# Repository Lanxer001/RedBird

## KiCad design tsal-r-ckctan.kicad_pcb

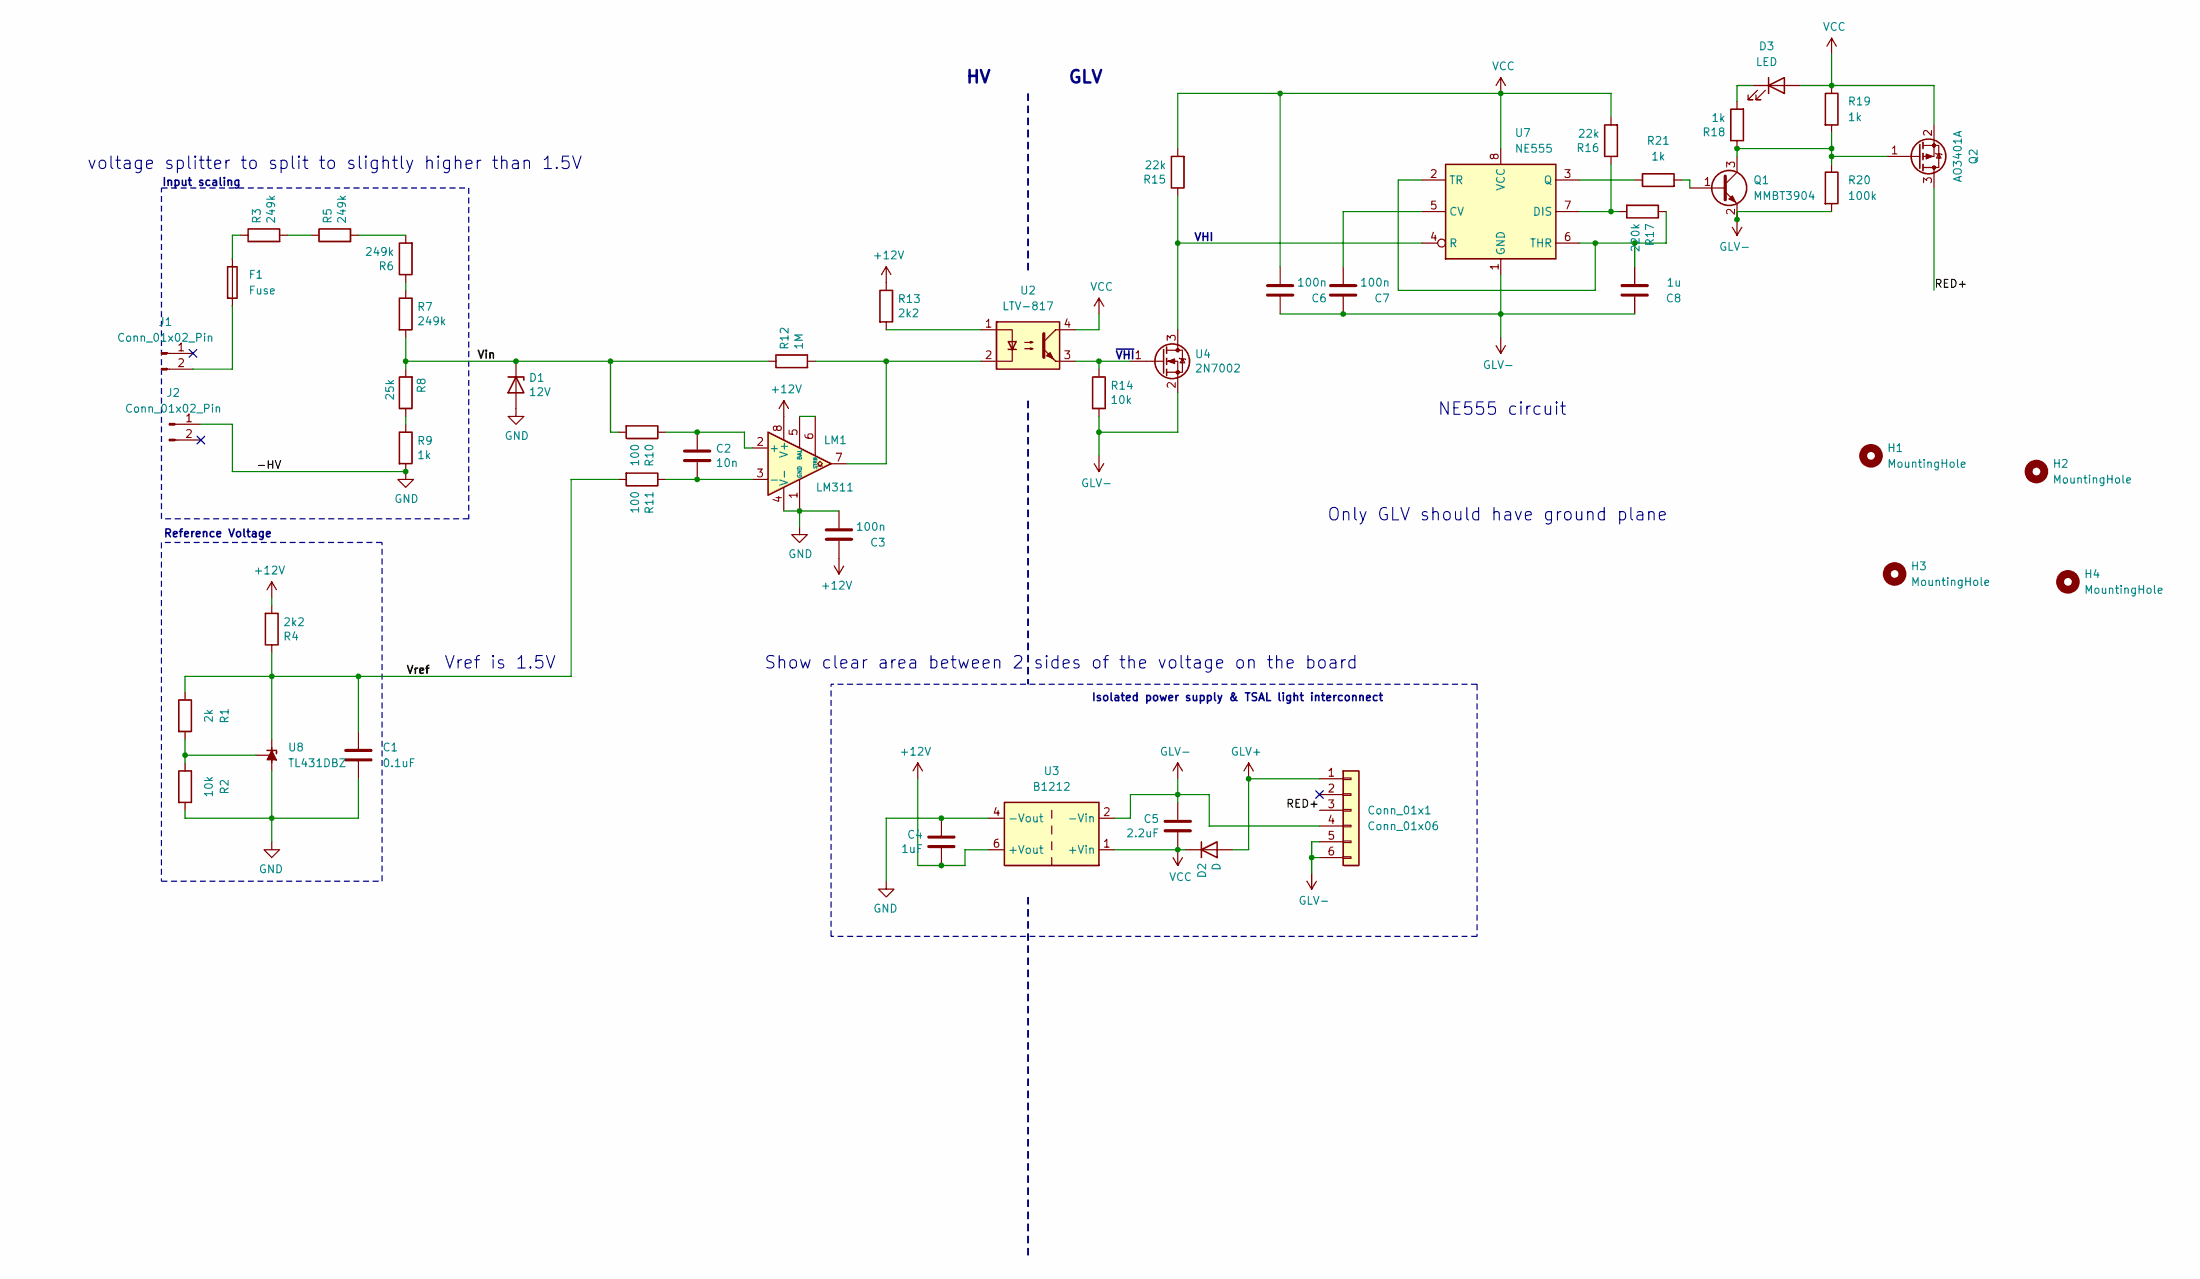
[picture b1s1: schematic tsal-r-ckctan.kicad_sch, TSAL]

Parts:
C1: 0.1uF; C_0805_2012Metric
C2: 10n; C_0805_2012Metric
C3, C6, C7: 100n; C_0805_2012Metric
C4: 1uF; C_0805_2012Metric
C5: 2.2uF; C_0805_2012Metric
C8: 1u; C_0805_2012Metric
Conn_01x1: Conn_01x06; JST_VH_B6P-VH_1x06_P3.96mm_Vertical
D1: 12V; D_DO-35_SOD27_P7.62mm_Horizontal
D2: D; D_SMA
D3: LED; LED_0805_2012Metric
F1: Fuse; Fuse_0805_2012Metric
H1, H2, H3, H4: MountingHole; MountingHole_2.2mm_M2
J1, J2: Conn_01x02_Pin; AMASS_XT60-M_1x02_P7.20mm_Vertical
LM1: LM311; LM311P
Q1: MMBT3904; SOT-23
Q2: AO3401A; SOT-23
R1: 2k; R_0805_2012Metric
R2, R14: 10k; R_0805_2012Metric
R3, R5, R6, R7: 249k; R_0805_2012Metric
R4, R13: 2k2; R_0805_2012Metric
R8: 25k; R_0805_2012Metric
R9, R18, R19, R21: 1k; R_0805_2012Metric
R10, R11: 100; R_0805_2012Metric
R12: 1M; R_0805_2012Metric
R15, R16: 22k; R_0805_2012Metric
R17: 220k; R_0805_2012Metric
R20: 100k; R_0805_2012Metric
U2: LTV-817; LTV-814
U3: B1212; Converter_DCDC_TRACO_TBA2-xxxx_Single_THT
U4: 2N7002; SOT-23TO-236_318-08_ONS
U7: NE555; SOIC-8_3.9x4.9mm_P1.27mm
U8: TL431DBZ; SOT-23

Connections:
+12V: C3.1, C4.2, LM1.8 (V+), R4.2, R13.1, U3.6 (+Vout)
/RED+: Conn_01x1.3, Q2.3 (D); also elsewhere on the board
/Vin: D1.1 (K), R7.2, R8.2, R10.2, R12.1
/Vref: C1.1, R1.1, R4.1, R11.2, U8.1 (K)
GLV+: Conn_01x1.1, D2.2 (A)
GLV-: C5.1, C6.1, C7.1, C8.1, Conn_01x1.4, Conn_01x1.5, Conn_01x1.6, Q1.2 (E), R14.2, R20.2, U3.2 (-Vin), U4.2 (S), U7.1 (GND); also elsewhere on the board
GND: C1.2, C3.2, C4.1, D1.2 (A), J2.1, LM1.1 (GND), LM1.4 (V-), R2.2, R9.2, U3.4 (-Vout), U8.3 (A)
unnamed: D3.1 (K), R18.2
unnamed: F1.1, R3.1
unnamed: F1.2, J1.2
unnamed: C2.1, LM1.2 (+), R10.1
unnamed: C2.2, LM1.3 (-), R11.1
unnamed: LM1.5 (BAL), LM1.6 (STRB)
unnamed: LM1.7, R12.2, U2.2
unnamed: Q1.1 (B), R21.2
unnamed: Q1.3 (C), Q2.1 (G), R18.1, R19.2, R20.1
unnamed: R3.2, R5.1
unnamed: R5.2, R6.2
unnamed: R6.1, R7.1
unnamed: R8.1, R9.1
unnamed: R13.2, U2.1
unnamed: R15.1, U4.3 (D), U7.4 (R)
unnamed: R14.1, U2.3, U4.1 (G)
unnamed: C7.2, U7.5 (CV)
unnamed: R16.1, R17.2, U7.7 (DIS)
unnamed: R21.1, U7.3 (Q)
unnamed: C8.2, R17.1, U7.2 (TR), U7.6 (THR)
unnamed: R1.2, R2.1, U8.2 (REF)
VCC: C5.2, C6.2, D2.1 (K), D3.2 (A), Q2.2 (S), R15.2, R16.2, R19.1, U2.4, U3.1 (+Vin), U7.8 (VCC)

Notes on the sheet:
voltage splitter to split to slightly higher than 1.5V
Show clear area between 2 sides of the voltage on the board
Isolated power supply & TSAL light interconnect
Reference Voltage
~{VHI}
Input scaling
Only GLV should have ground plane
GLV
VHI
Vref is 1.5V
NE555 circuit

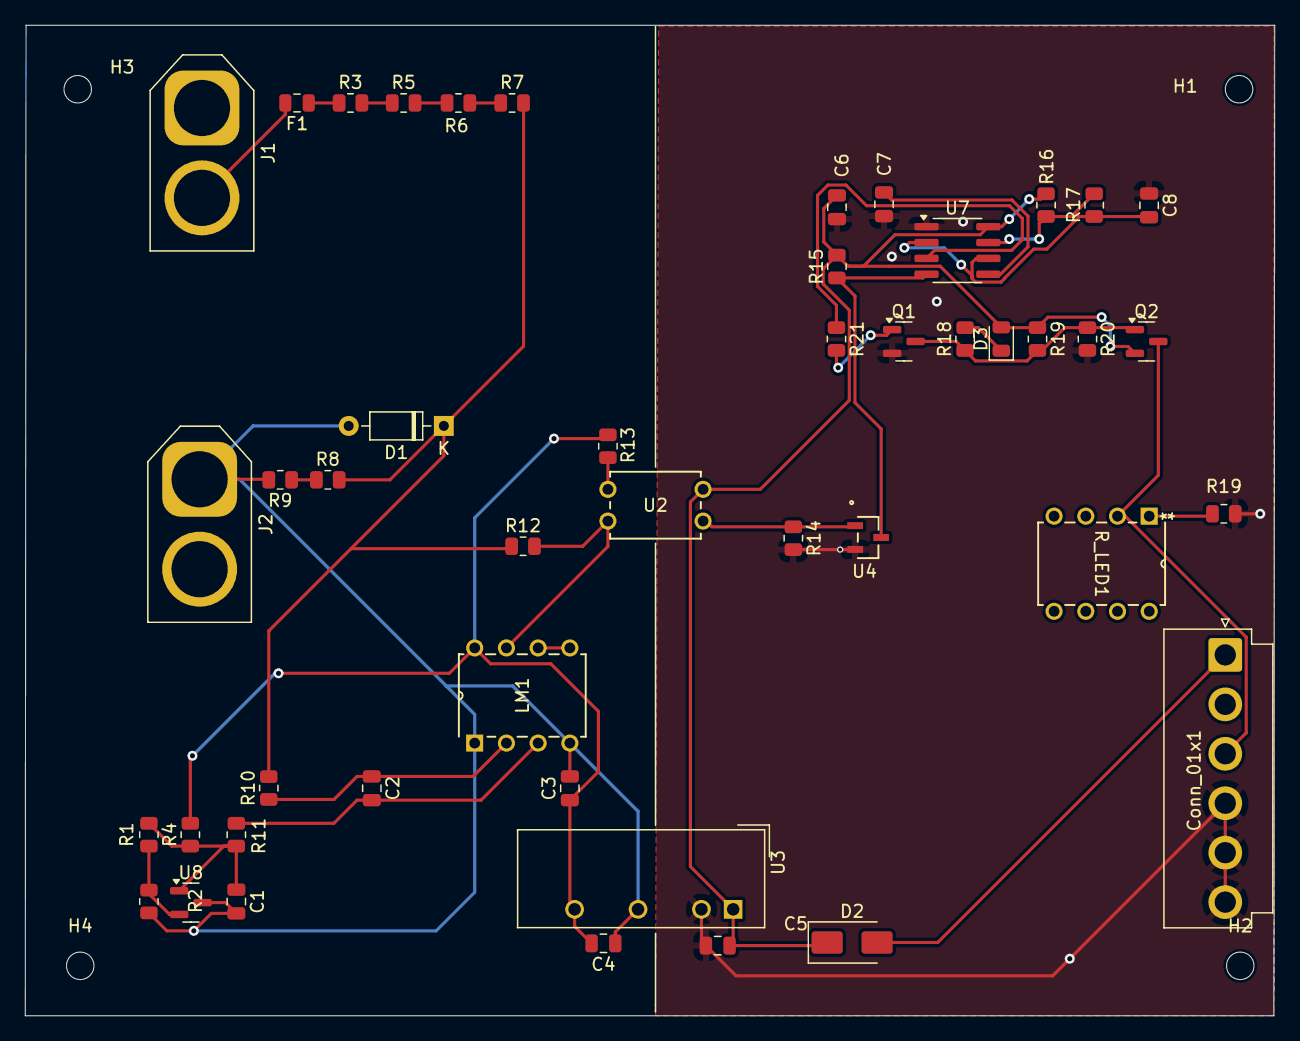
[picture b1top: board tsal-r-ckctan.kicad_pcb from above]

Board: 2 copper layers, 100.1 x 79.3 mm, 50 parts (0 on the bottom side), 30 nets.

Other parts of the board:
R19#2: 2k2; R_0805_2012Metric
R_LED1: VHI; P8

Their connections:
/RED+: R_LED1.2 (A); also elsewhere on the board
GLV-: R19#2.2; also elsewhere on the board
unnamed: R19#2.1, R_LED1.1 (K)
